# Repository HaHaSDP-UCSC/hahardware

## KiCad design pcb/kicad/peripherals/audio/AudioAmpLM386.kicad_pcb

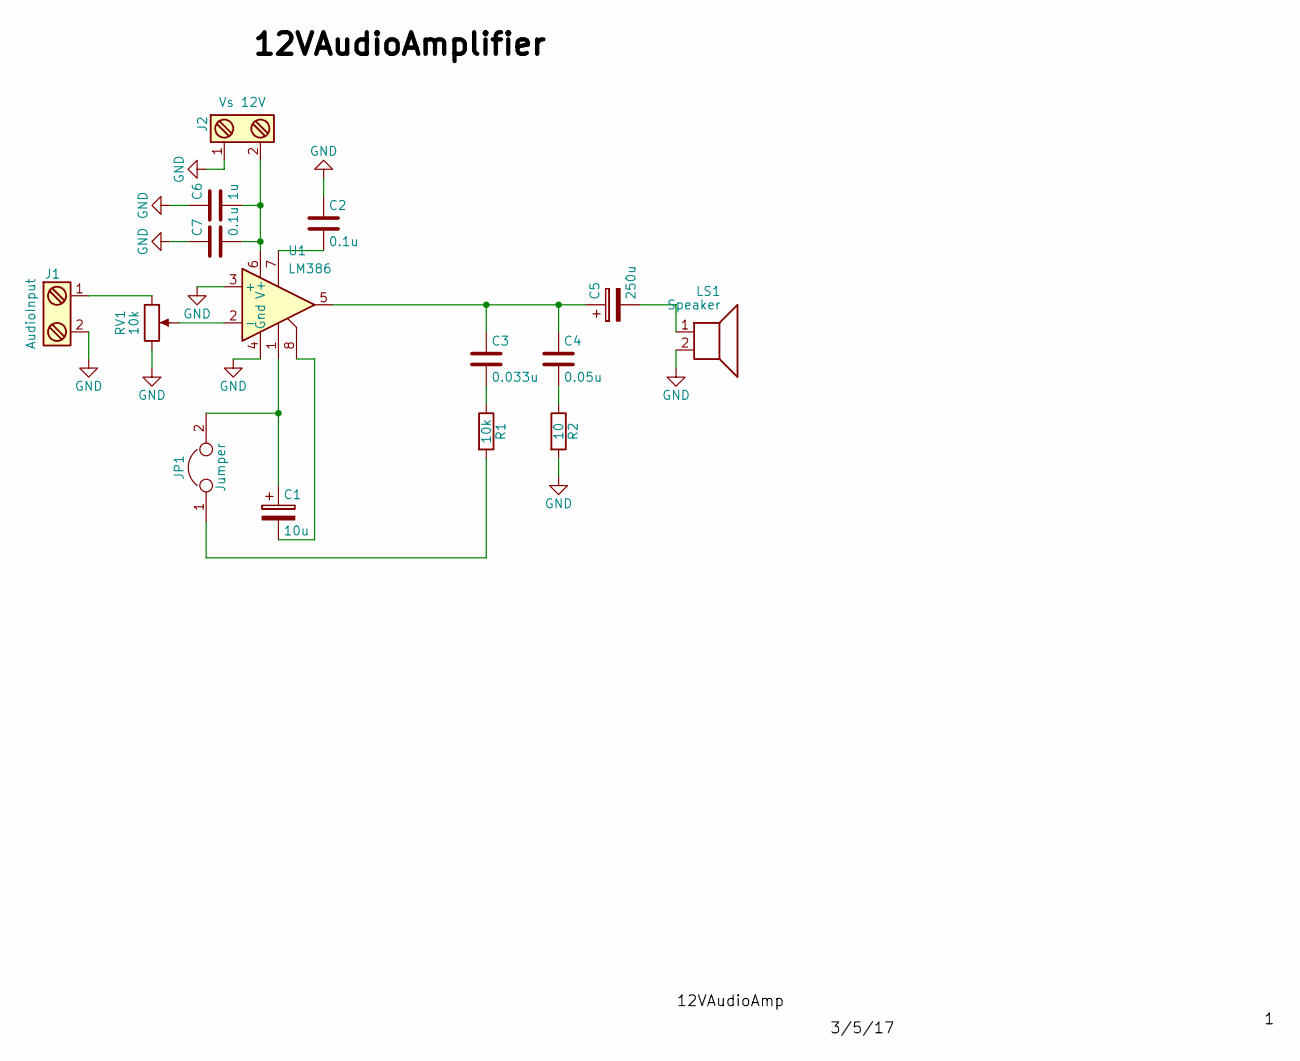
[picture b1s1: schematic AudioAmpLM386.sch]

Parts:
C1: 10u; CP_Elec_5x4.5
C2, C7: 0.1u; C_0603_HandSoldering
C3: 0.033u; C_0805_HandSoldering
C4: 0.05u; C_0805_HandSoldering
C5: 250u; CP_Elec_10x10
C6: 1u; C_0805_HandSoldering
J1: AudioInput; Pin_Header_Straight_1x02_Pitch2.54mm
J2: Vs 12V; Pin_Header_Straight_1x02_Pitch2.54mm
JP1: Jumper; Pin_Header_Straight_1x02_Pitch2.54mm
LS1: Speaker; Pin_Header_Straight_1x02_Pitch2.54mm
R1: 10k; R_0805_HandSoldering
R2: 10; R_0805_HandSoldering
RV1: 10k; Potentiometer_Alps_RK09K_Horizontal
U1: LM386; DIP-8_W7.62mm

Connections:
GND: C2.1, C6.1, C7.1, J1.2, J2.1, LS1.2, R2.2, RV1.3, U1.3 (+), U1.4 (Gnd)
unnamed: C1.1, JP1.2, U1.1
unnamed: C1.2, U1.8
unnamed: C2.2, U1.7
unnamed: C3.1, C4.1, C5.1, U1.5
unnamed: C3.2, R1.1
unnamed: C4.2, R2.1
unnamed: C5.2, LS1.1
unnamed: C6.2, C7.2, J2.2, U1.6 (V+)
unnamed: J1.1, RV1.1
unnamed: JP1.1, R1.2
unnamed: RV1.2, U1.2 (-)

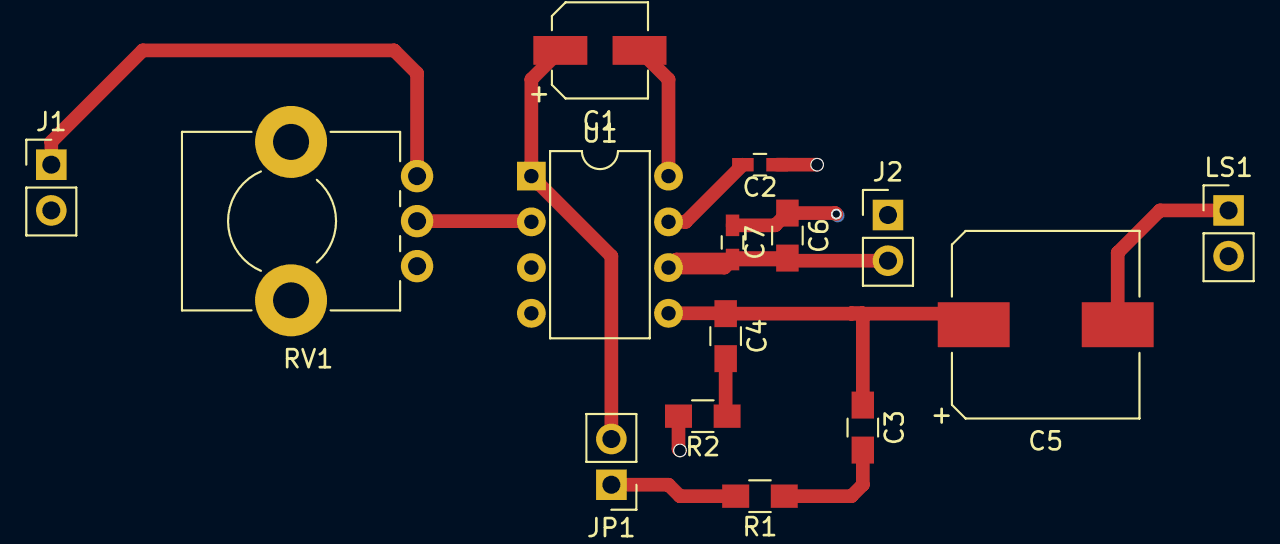
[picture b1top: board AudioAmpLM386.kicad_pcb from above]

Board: 2 copper layers, 15 parts (0 on the bottom side), 12 nets.

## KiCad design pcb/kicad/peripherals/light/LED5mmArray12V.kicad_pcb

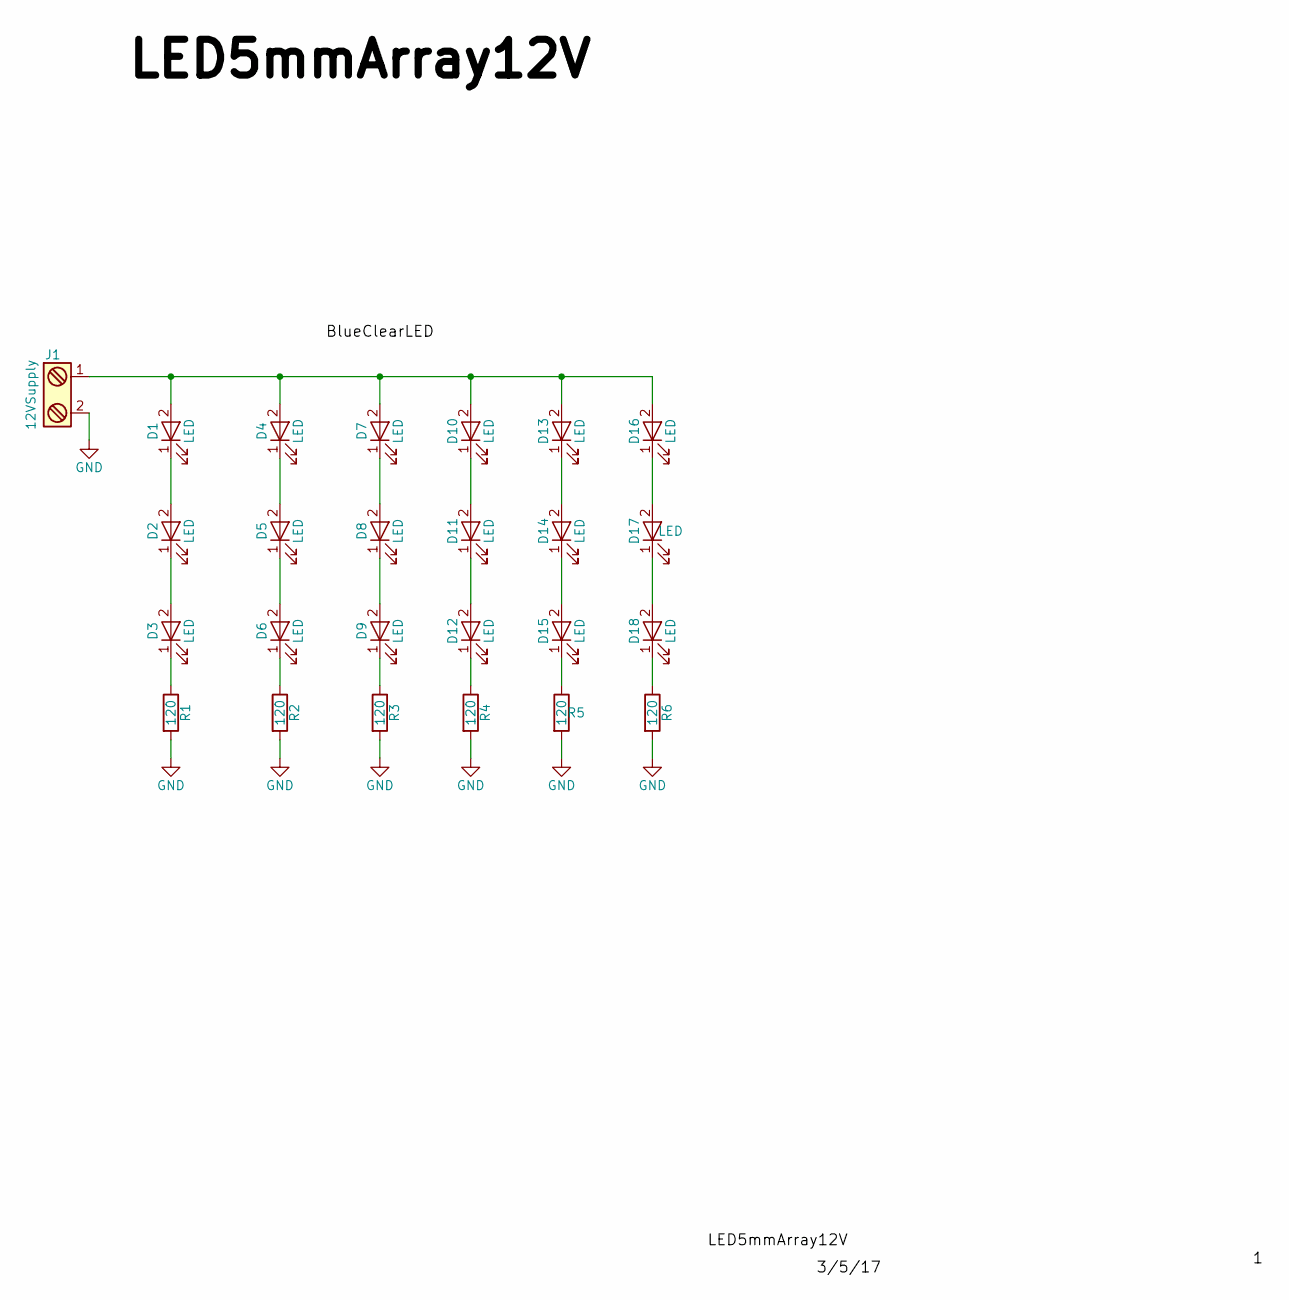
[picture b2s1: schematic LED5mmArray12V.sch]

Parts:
D1, D2, D3, D4, D5, D6, D7, D8, D9, D10, D11, D12, D13, D14, D15, D16, D17, D18: LED; LED_D5.0mm
J1: 12VSupply; Pin_Header_Straight_1x02_Pitch2.54mm
R1, R2, R3, R4, R5, R6: 120; R_0603_HandSoldering

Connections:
GND: J1.2, R1.2, R2.2, R3.2, R4.2, R5.2, R6.2
unnamed: D1.1 (K), D2.2 (A)
unnamed: D1.2 (A), D4.2 (A), D7.2 (A), D10.2 (A), D13.2 (A), D16.2 (A), J1.1
unnamed: D2.1 (K), D3.2 (A)
unnamed: D3.1 (K), R1.1
unnamed: D4.1 (K), D5.2 (A)
unnamed: D5.1 (K), D6.2 (A)
unnamed: D6.1 (K), R2.1
unnamed: D7.1 (K), D8.2 (A)
unnamed: D8.1 (K), D9.2 (A)
unnamed: D9.1 (K), R3.1
unnamed: D10.1 (K), D11.2 (A)
unnamed: D11.1 (K), D12.2 (A)
unnamed: D12.1 (K), R4.1
unnamed: D13.1 (K), D14.2 (A)
unnamed: D14.1 (K), D15.2 (A)
unnamed: D15.1 (K), R5.1
unnamed: D16.1 (K), D17.2 (A)
unnamed: D17.1 (K), D18.2 (A)
unnamed: D18.1 (K), R6.1

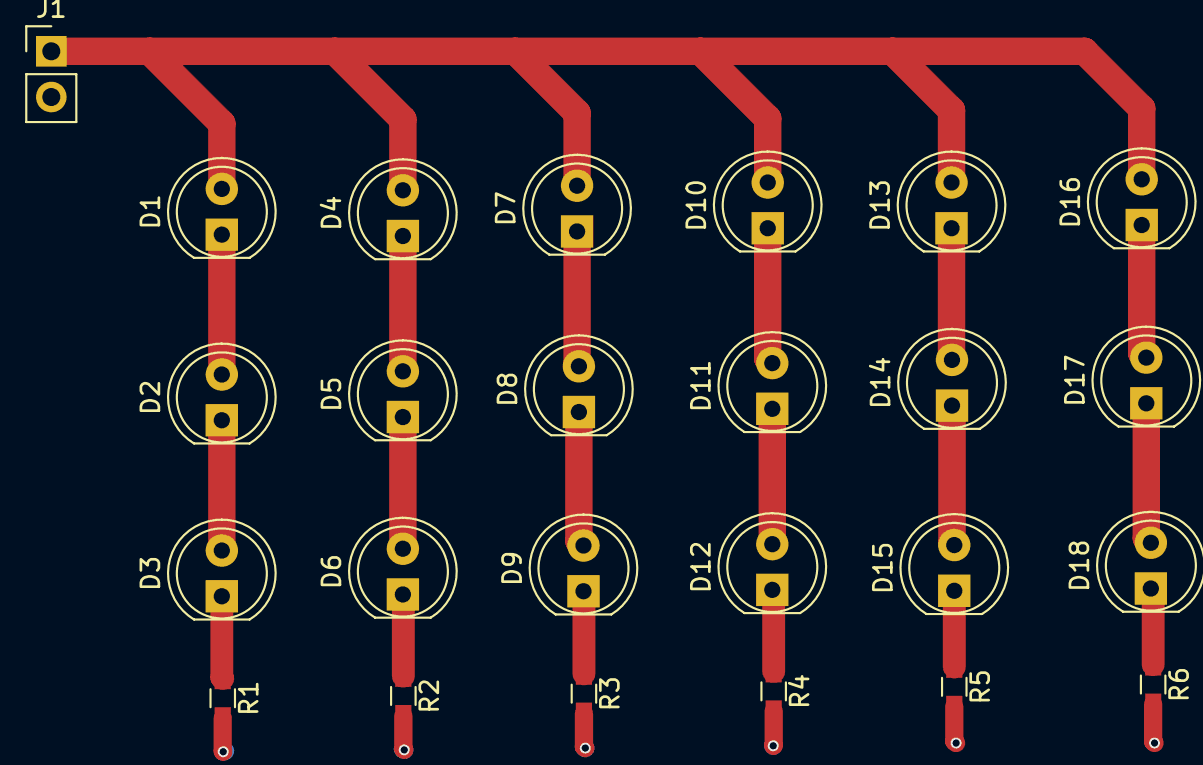
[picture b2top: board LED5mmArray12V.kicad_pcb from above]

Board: 2 copper layers, 25 parts (0 on the bottom side), 20 nets.

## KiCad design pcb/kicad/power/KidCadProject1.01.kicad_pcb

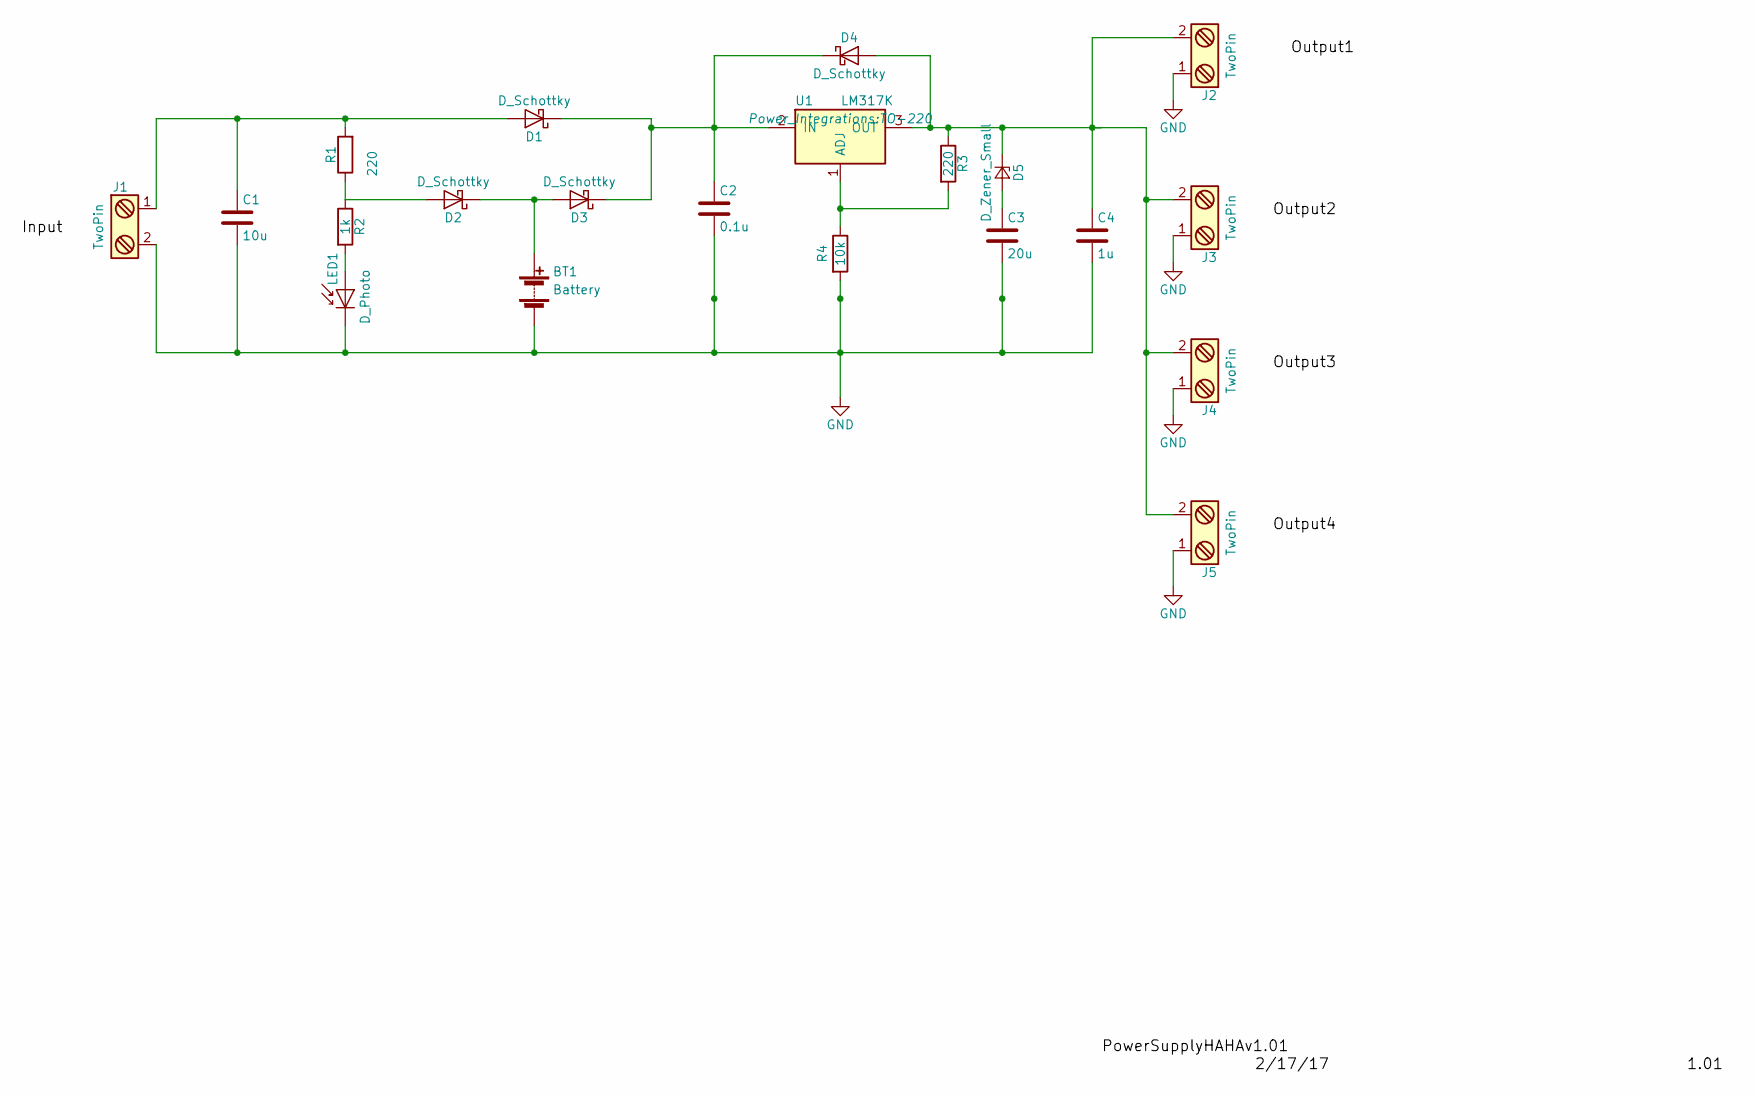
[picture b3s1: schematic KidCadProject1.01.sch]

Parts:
BT1: Battery; Pin_Header_Straight_1x02_Pitch2.54mm
C1: 10u; C_1206_HandSoldering
C2: 0.1u; C_1206_HandSoldering
C3: 20u; C_2220_HandSoldering
C4: 1u; C_1206_HandSoldering
D1, D2, D3, D4: D_Schottky; D_DO-201_P15.24mm_Horizontal
D5: D_Zener_Small; D_DO-201_P15.24mm_Horizontal
J1, J2, J3, J4, J5: TwoPin; Pin_Header_Straight_1x02_Pitch2.54mm
LED1: D_Photo; D_DO-201AD_P15.24mm_Horizontal
R1, R3: 220; R_2512_HandSoldering
R2: 1k; R_2512_HandSoldering
R4: 10k; R_2512_HandSoldering
U1: LM317K; TO-220

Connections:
GND: BT1.2 (-), C1.2, C2.2, C3.2, C4.2, J1.2, J2.1, J3.1, J4.1, J5.1, LED1.1 (K), R4.2
unnamed: BT1.1 (+), D2.1 (K), D3.2 (A)
unnamed: C1.1, D1.2 (A), J1.1, R1.2
unnamed: C2.1, D1.1 (K), D3.1 (K), D4.1 (K), U1.2 (IN)
unnamed: C3.1, D5.2 (A)
unnamed: C4.1, D4.2 (A), D5.1 (K), J2.2, J3.2, J4.2, J5.2, R3.1, U1.3 (OUT)
unnamed: D2.2 (A), R1.1, R2.1
unnamed: LED1.2 (A), R2.2
unnamed: R3.2, R4.1, U1.1 (ADJ)

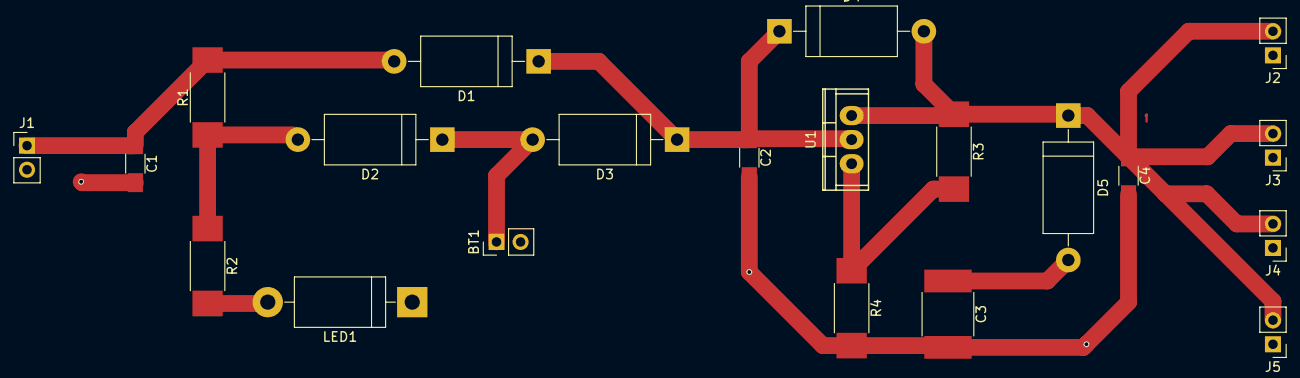
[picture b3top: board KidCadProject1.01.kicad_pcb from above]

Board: 2 copper layers, 21 parts (0 on the bottom side), 9 nets.
